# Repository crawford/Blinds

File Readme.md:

#Blinds#

##Hardware##
Uses Zigbee for all logic and communication.
8-channel servo controller.

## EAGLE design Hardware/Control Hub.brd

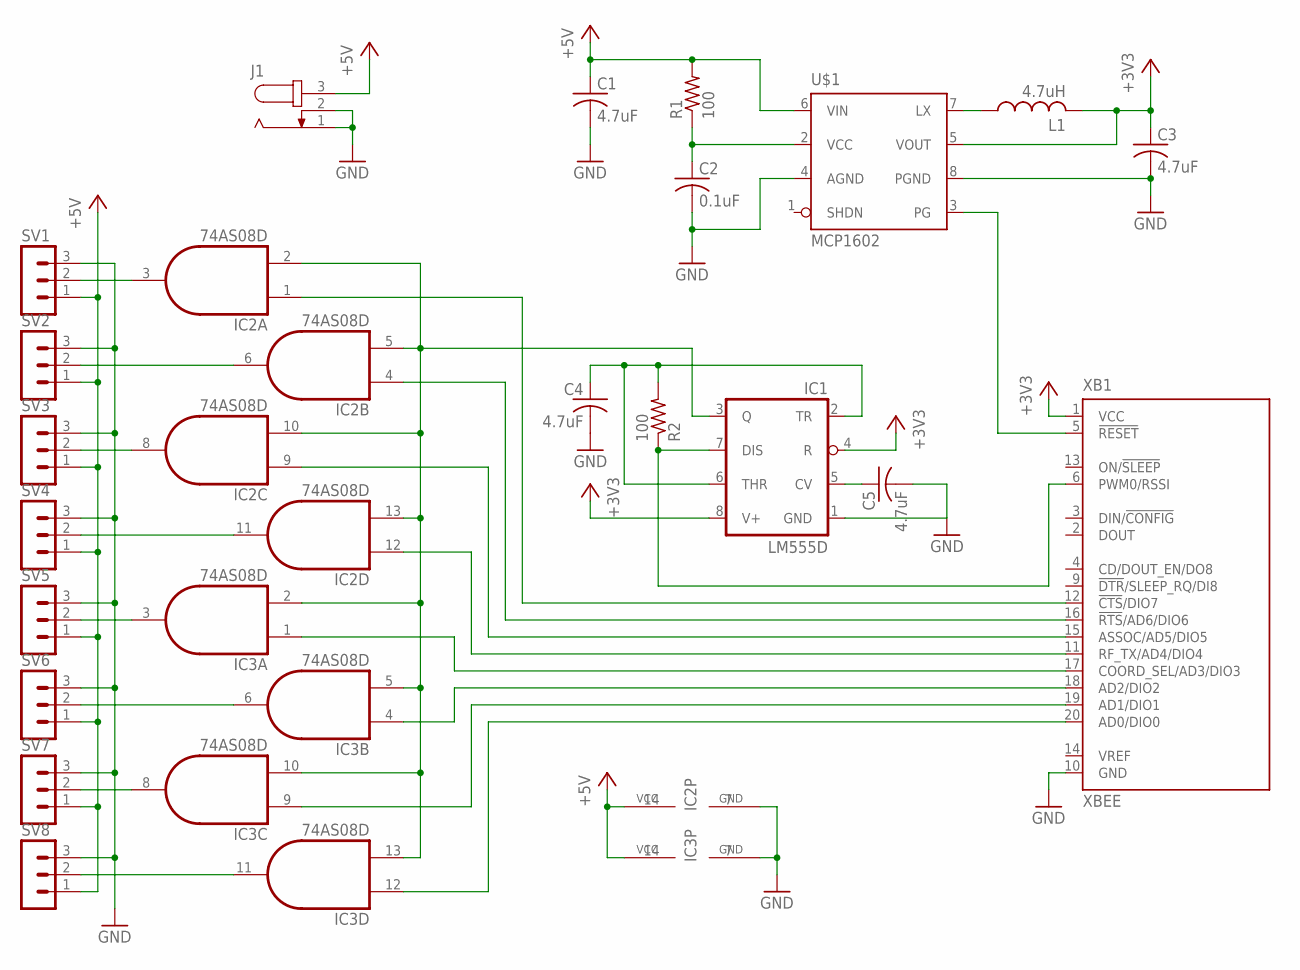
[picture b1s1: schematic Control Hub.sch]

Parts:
C1, C3, C4, C5: 4.7uF; C050-030X075
C2: 0.1uF; C050-030X075
IC1: LM555D; SO08
IC2, IC3: 74AS08D; SO14
J1: JACK-PLUG1; SPC4078
L1: 4.7uH; L3216C
R1, R2: 100; M3216
SV1, SV2, SV3, SV4, SV5, SV6, SV7, SV8: MA03-1
U$1: MCP1602; MSOP08
XB1: XBEE

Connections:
+3V3: IC1.4 (R), IC1.8 (V+), XB1.1 (VCC)
+5V: C1.1, IC2.14 (VCC), IC3.14 (VCC), J1.3, R1.2, SV1.1, SV2.1, SV3.1, SV4.1, SV5.1, SV6.1, SV7.1, SV8.1, U$1.6 (VIN)
GND: C1.2, C2.2, C3.2, C4.2, C5.2, IC1.1 (GND), IC2.7 (GND), IC3.7 (GND), J1.1, J1.2, SV1.3, SV2.3, SV3.3, SV4.3, SV5.3, SV6.3, SV7.3, SV8.3, U$1.4 (AGND), U$1.8 (PGND), XB1.10 (GND)
unnamed: IC2.3 (O), SV1.2
unnamed: IC2.6 (O), SV2.2
unnamed: IC2.8 (O), SV3.2
unnamed: IC2.11 (O), SV4.2
unnamed: IC3.3 (O), SV5.2
unnamed: IC3.6 (O), SV6.2
unnamed: IC3.8 (O), SV7.2
unnamed: IC3.11 (O), SV8.2
unnamed: C5.1, IC1.5 (CV)
unnamed: IC3.12 (I0), XB1.20 (AD0/DIO0)
unnamed: IC3.9 (I0), XB1.19 (AD1/DIO1)
unnamed: IC3.4 (I0), XB1.18 (AD2/DIO2)
unnamed: IC3.1 (I0), XB1.17 (COORD_SEL/AD3/DIO3)
unnamed: IC2.12 (I0), XB1.11 (RF_TX/AD4/DIO4)
unnamed: IC2.9 (I0), XB1.15 (ASSOC/AD5/DIO5)
unnamed: IC2.4 (I0), XB1.16 (!RTS!/AD6/DIO6)
unnamed: IC2.1 (I0), XB1.12 (!CTS!/DIO7)
unnamed: U$1.3 (PG), XB1.5 (!RESET)
unnamed: L1.1, U$1.7 (LX)
unnamed: C4.1, IC1.2 (TR), IC1.6 (THR), R2.2
unnamed: C2.1, R1.1, U$1.2 (VCC)
unnamed: IC1.3 (Q), IC2.2 (I1), IC2.5 (I1), IC2.10 (I1), IC2.13 (I1), IC3.2 (I1), IC3.5 (I1), IC3.10 (I1), IC3.13 (I1)
unnamed: IC1.7 (DIS), R2.1, XB1.6 (PWM0/RSSI)
VOUT: C3.1, L1.2, U$1.5 (VOUT)

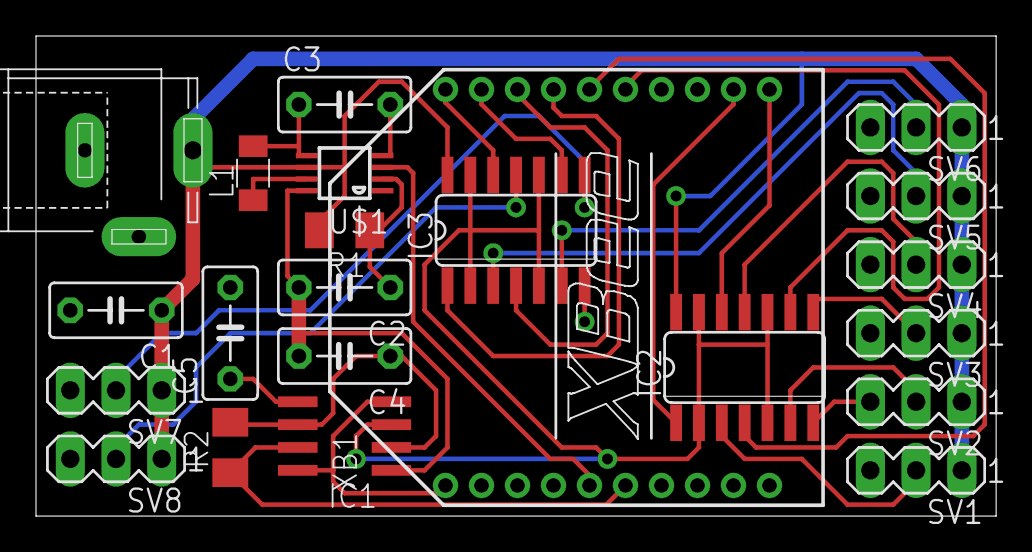
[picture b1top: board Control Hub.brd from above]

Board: 2 copper layers, 53.3 x 26.7 mm, 22 parts (0 on the bottom side), 27 nets.

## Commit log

2012-07-26 Initial Commit
    Added readme
2012-07-26 Initial board design
    Added initial schematic and board layout.
2012-07-28 Fixed board sizing and added logo
    Added gitignore as well
